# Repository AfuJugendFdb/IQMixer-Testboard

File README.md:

# IQMixer-Testboard
Testboard for LTC5598 IQ-Mixer

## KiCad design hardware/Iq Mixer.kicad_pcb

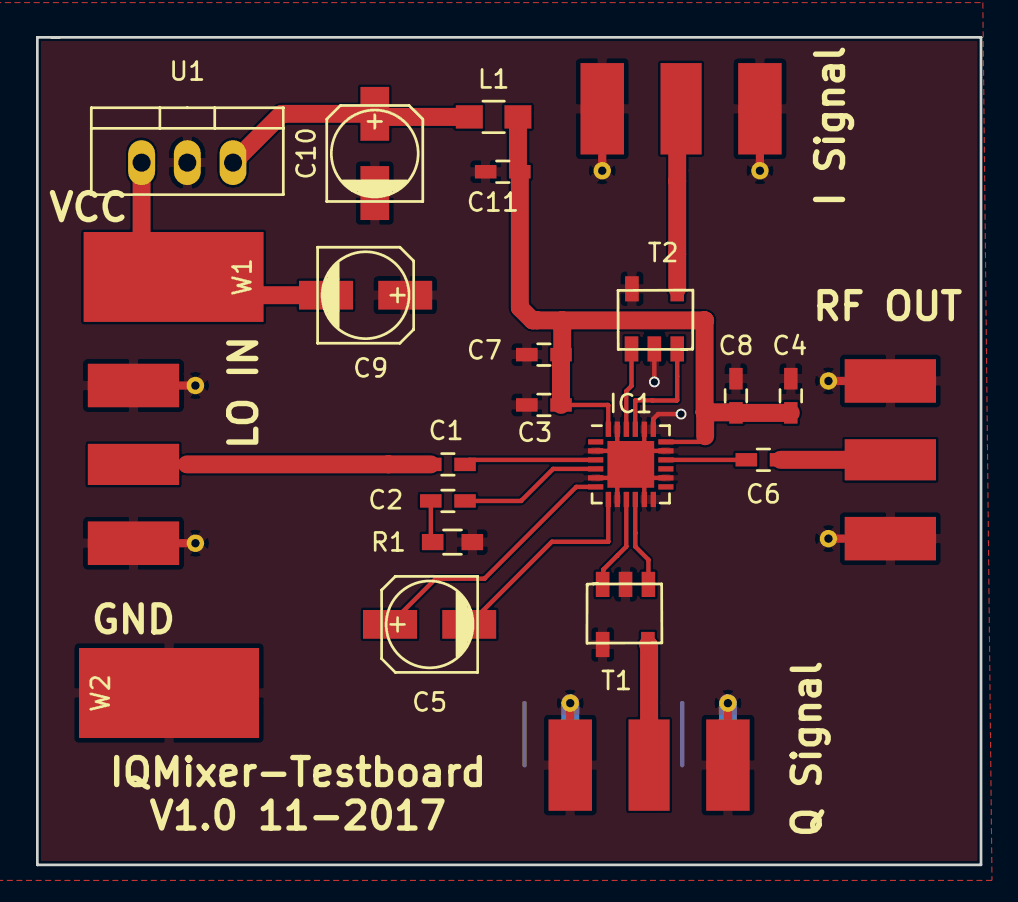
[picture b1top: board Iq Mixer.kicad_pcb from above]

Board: 2 copper layers, 52.4 x 46.0 mm, 23 parts (0 on the bottom side), 18 nets.

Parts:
C1, C2, C6: 10nF; C_0603_HandSoldering
C3, C8: 1nF; C_0603_HandSoldering
C4: 100n; C_0603_HandSoldering
C5: 470nF; c_elec_5x5.3
C7, C11: 100nF; C_0603_HandSoldering
C9, C10: 1uF; c_elec_5x5.3
IC1: LTC5598; QFN-24-1EP_4x4mm_Pitch0.5mm
L1: 20uH; R_0805_HandSoldering
P1: SMA_LO; Molex_SMA_Jack_Edge_Mount
P2: SMA_I; Molex_SMA_Jack_Edge_Mount
P3: SMA_Q; Molex_SMA_Jack_Edge_Mount
P4: SMA_OUT; Molex_SMA_Jack_Edge_Mount
R1: 50Ohm; R_0603_HandSoldering
T1, T2: TRANSFO4; Balun
U1: 7805; TO-220_Neutral123_Vertical
W1: VIN; SolderWirePad_single_SMD_5x10mm
W2: VGND; SolderWirePad_single_SMD_5x10mm

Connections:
GND: C3.2, C4.2, C7.2, C8.2, C9.1, C10.2, C11.1, IC1.2, IC1.5, IC1.8, IC1.11, IC1.12, IC1.14, IC1.17, IC1.19, IC1.20, IC1.23, IC1.25, P1.2, P2.2, P3.2, P4.2, R1.1, T1.2, T1.5, T2.2, T2.4, U1.2, W2.1
unnamed: C1.1, IC1.3
unnamed: C1.2, P1.1
unnamed: C2.1, IC1.4
unnamed: C2.2, R1.2
unnamed: C5.1, IC1.6
unnamed: C5.2, IC1.7
unnamed: C6.1, P4.1
unnamed: C6.2, IC1.16
unnamed: C9.2, U1.1, W1.1
unnamed: C10.1, L1.1, U1.3
unnamed: IC1.9, T1.1
unnamed: IC1.10, T1.3
unnamed: IC1.21, T2.1
unnamed: IC1.22, T2.3
unnamed: P2.1, T2.5
unnamed: P3.1, T1.4
VCC: C3.1, C4.1, C7.1, C8.1, C11.2, IC1.18, IC1.24, L1.2

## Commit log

2017-11-04 Schematics of board added
2017-11-04 Footprint-association
2017-11-06 SMA connector footprint added
2017-11-11 Layout, Gerber
2017-11-13 Various little improvements in layout, Silkscreen Hints, Gerber generated
